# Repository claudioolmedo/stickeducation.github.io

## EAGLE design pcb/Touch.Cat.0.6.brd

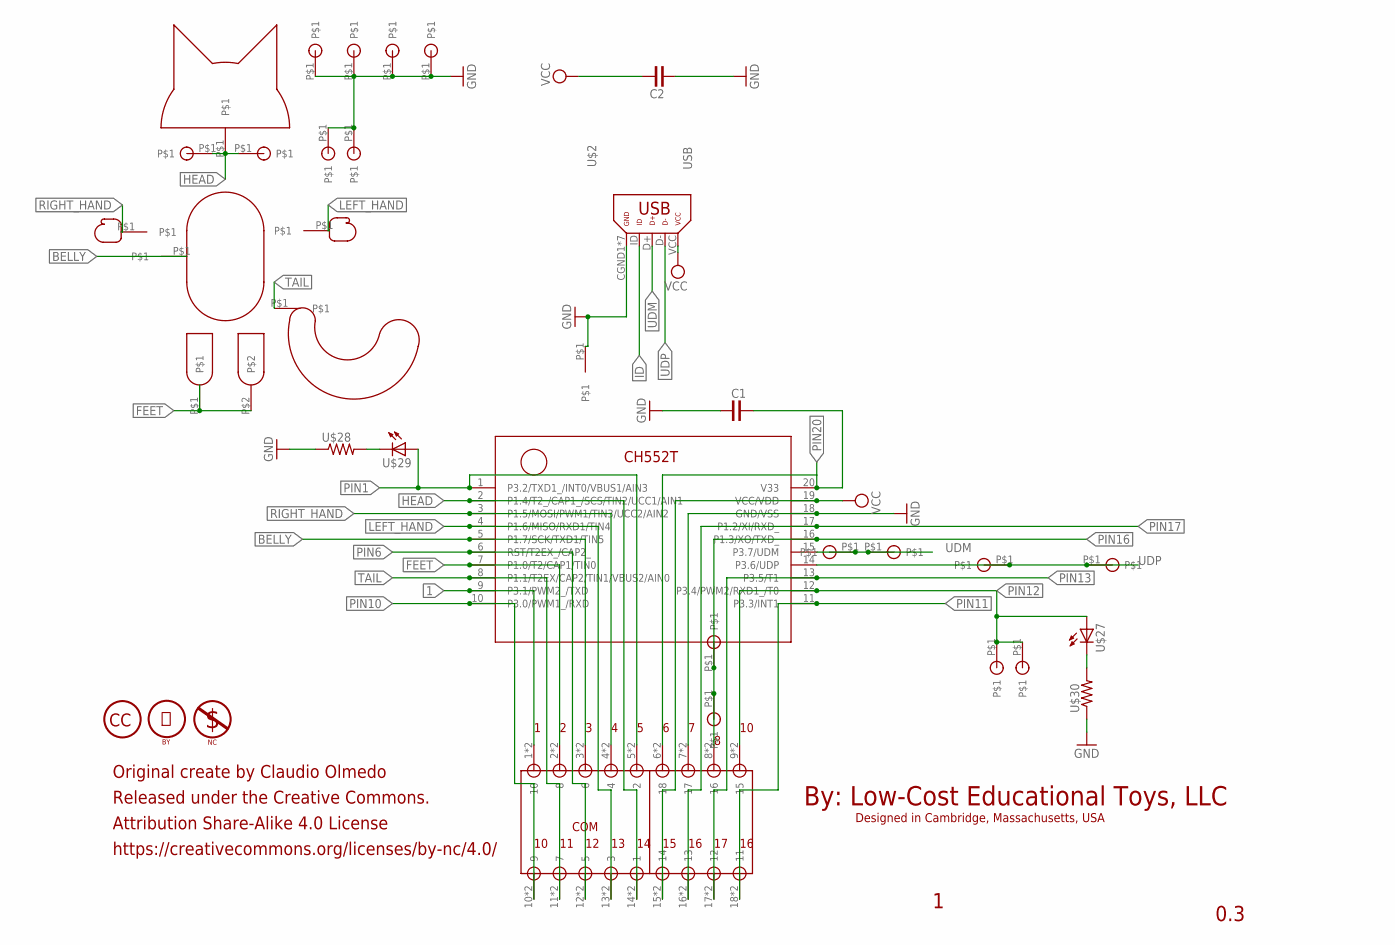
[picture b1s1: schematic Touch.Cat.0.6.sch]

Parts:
C1, C2: CAPACITOR; C0402
U$1: CHIP-TOUCH-CAT; TSSOP20
U$2: USB; GHI-CONNECTORS_10118192-0001LF(MICRO-USB-B-AMPHENOL-FCI)
U$3, U$5, U$6, U$7, U$8, U$9, U$11, U$12, U$13, U$14, U$15, U$16, U$23, U$24, U$25, U$26: PADVIA
U$4: COM-TOUCH-CAT; COM
U$17: HEAD-TOUCH-CAT
U$18: BELLY-TOUCH-CAT
U$19: RIGHT_HAND-TOUCH-CAT
U$20: LEFT_HAND-TOUCH-CAT
U$21: FEET-TOUCH-CAT
U$22: TAIL-TOUCH-CAT
U$27, U$29: LED-TOUCH-CAT; 0603-ORANGE
U$28, U$30: RESISTOR-TOUCH-CAT; R0402
U$31: OSHW-LOGO; OSHW-LOGO-MINI
U$33: ABOUT-TOUCH-CAT

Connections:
1: U$1.9 (P3.1/PWM2_/TXD), U$4.1 (10), U$4.1.1 (10)
BELLY: U$1.5 (P1.7/SCK/TXD1/TIN5), U$4.3 (6), U$4.3.1 (6), U$18.P$1
FEET: U$1.7 (P1.0/T2/CAP1/TIN0), U$4.2 (8), U$4.2.1 (8), U$21.P$1, U$21.P$2
GND: C1.1, C2.1, U$1.18 (GND/VSS), U$2.CGND1 (GND), U$2.CGND2 (GND), U$2.CGND3 (GND), U$2.CGND4 (GND), U$2.CGND5 (GND), U$2.CGND6 (GND), U$2.GND, U$4.7 (17), U$4.7.1 (17), U$6.P$1, U$7.P$1, U$23.P$1, U$24.P$1, U$25.P$1, U$26.P$1, U$28.1, U$30.1, U$31.P$1
HEAD: U$1.2 (P1.4/T2_/CAP1_/SCS/TIN2/UCC1/AIN1), U$4.14 (1), U$4.14.1 (1), U$8.P$1, U$9.P$1, U$17.P$1
ID: U$2.ID
LEFT_HAND: U$1.4 (P1.6/MISO/RXD1/TIN4), U$4.13 (3), U$4.13.1 (3), U$20.P$1
unnamed: U$27.C, U$30.2
unnamed: U$28.2, U$29.C
PIN1: U$1.1 (P3.2/TXD1_/INT0/VBUS1/AIN3), U$4.5 (2), U$4.5.1 (2), U$29.A
PIN6: U$1.6 (RST/T2EX_/CAP2_), U$4.12 (5), U$4.12.1 (5)
PIN10: U$1.10 (P3.0/PWM1_/RXD), U$4.10 (9), U$4.10.1 (9)
PIN11: U$1.11 (P3.3/INT1), U$4.18 (11), U$4.18.1 (11)
PIN12: U$1.12 (P3.4/PWM2/RXD1_/T0), U$3.P$1, U$4.9 (15), U$4.9.1 (15), U$5.P$1, U$27.A
PIN13: U$1.13 (P3.5/T1), U$4.17 (12), U$4.17.1 (12)
PIN16: U$1.16 (P1.3/XO/TXD_), U$4.8 (16), U$4.8.1 (16), U$11.P$1, U$12.P$1
PIN17: U$1.17 (P1.2/XI/RXD_), U$4.16 (13), U$4.16.1 (13)
PIN20: C1.2, U$1.20 (V33), U$4.6 (18), U$4.6.1 (18)
RIGHT_HAND: U$1.3 (P1.5/MOSI/PWM1/TIN3/UCC2/AIN2), U$4.4, U$4.4.1 (4), U$19.P$1
TAIL: U$1.8 (P1.1/T2EX/CAP2/TIN1/VBUS2/AIN0), U$4.11 (7), U$4.11.1 (7), U$22.P$1
UDM: U$1.15 (P3.7/UDM), U$2.D+, U$13.P$1, U$14.P$1
UDP: U$1.14 (P3.6/UDP), U$2.D-, U$15.P$1, U$16.P$1
VCC: C2.2, U$1.19 (VCC/VDD), U$2.VCC, U$4.15 (14), U$4.15.1 (14)

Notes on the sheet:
By: Low-Cost Educational Toys, LLC
0.3
Released under the Creative Commons.
Attribution Share-Alike 4.0 License
https://creativecommons.org/licenses/by-nc/4.0/
Designed in Cambridge, Massachusetts, USA
Original create by Claudio Olmedo

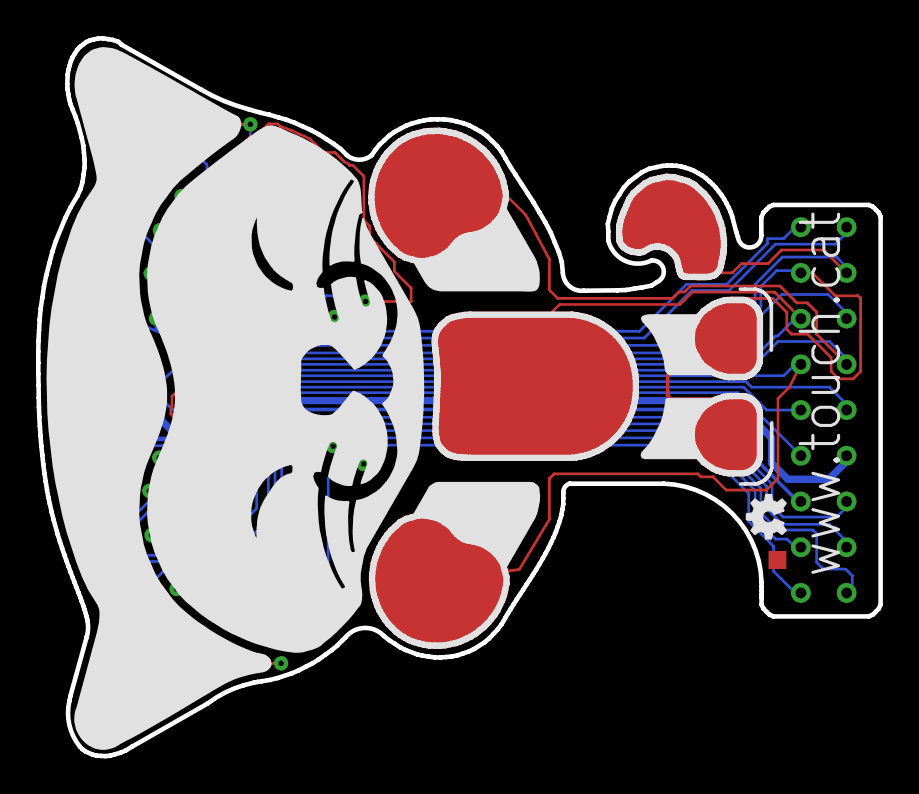
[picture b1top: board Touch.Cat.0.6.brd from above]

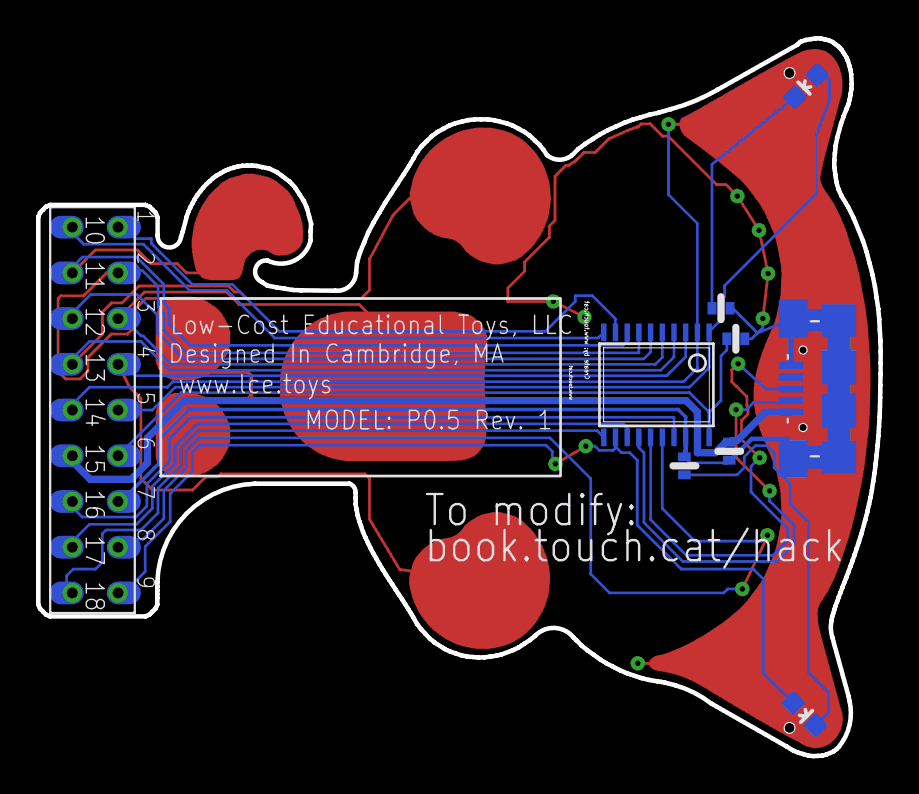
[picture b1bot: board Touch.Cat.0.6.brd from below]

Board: 2 copper layers, 46.8 x 39.9 mm, 33 parts (8 on the bottom side), 22 nets.

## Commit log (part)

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2024-06-09 FORK Button
2024-06-09 Add button
2024-06-09 Revert "Forked project"
    This reverts commit 219d94ef014467ebf30caa72584da5fcda3c1e21.
2024-06-09 add front
2024-06-09 move button
2024-06-09 Revert "add button idFORK"
    This reverts commit b50f3598abbacb2bd795d2f7a53b1b00e5fdfc06.
2024-06-09 Test new rule firebase users
2024-06-09 Update Auth
2024-06-09 Create new link for FORK project
2024-06-10 hide the project button
2024-06-10 add testing Toolbar check
2024-06-10 update the Toolbar component to handle updates:
2024-06-10 Add firebaseDB on the import firebase.js
2024-06-10 Eliminate extra fork-button
2024-06-10 Fixed updateToolbar
2024-06-10 import onAuthStateChanged
2024-06-10 Revert "import onAuthStateChanged"
    This reverts commit 32ab2515ec3ae102df96d2c6f08f525b48d4f2a7.
2024-06-10 Revert "Fixed updateToolbar"
    This reverts commit 9526200dc3caa174453517c8802cb499c4305fc2.
2024-06-10 Revert "Eliminate extra fork-button"
    This reverts commit fc2680cc5e8c61a388a43700ec2df0a8b60bbb7c.
2024-06-10 Revert "Add firebaseDB on the import firebase.js"
    This reverts commit a5adabc3d3b3c61c061e45b345f50feb31baf269.
2024-06-10 Revert "update the Toolbar component to handle updates:"
    This reverts commit 9eae6e9ea8d92e4afd520da7d7ba90d4c10669d5.
2024-06-10 Revert "add testing Toolbar check"
    This reverts commit 8379b6e62155da6a67168fa24b028ce01dee41c7.
2024-06-10 Revert "hide the project button"
    This reverts commit 7fb295577483180540f44946e63964561fc119aa.
2024-06-10 Revert "Create new link for FORK project"
    This reverts commit 3ffa41b829527fd2d067b3f9cf1703cd6e71bc2b.
2024-06-10 Revert "Update Auth"
    This reverts commit 1d60ee014545bdae6d5c83d66f463427ddb29715.
2024-06-10 Revert "Test new rule firebase users"
    This reverts commit ca458df6e727259e23f9f14e1785f46fbf466d3e.
2024-06-10 Reapply "add button idFORK"
    This reverts commit b23b4df315eb198e66cc026fbcea6e85784686de.
2024-06-10 Add ownerId to projects
2024-06-10 "FORK" Button to Toolbar (left side)
2024-06-11 test ownerId
2024-06-11 Revert "Owner or Not"
    This reverts commit b46a69bae10a3ede2311c328d27bbfe17839de37.
2024-06-11 NO OWNER
2024-06-11 is Read Only for no USER
2024-06-11 test no save in firebase if no owner
2024-06-11 Reapply "is Read Only for no USER"
    This reverts commit 5f43690326c5c1d3f3589c3cff659b61ccf89738.
2024-06-11 Revert "fixed bug"
    This reverts commit 88be0c6a9abc40043deaa7fb00c31d44cb79375a.
2024-06-11 forkAction solve bug FORK Button
2024-06-11 Revert "Fixed bug"
    This reverts commit ce5844383ee78a539affbb674f9df05b92d11cbc.
2024-06-11 test owner test
2024-06-11 Revert "fixed bug for have owner"
    This reverts commit 856ea7a18c79d134ad57414714e734facb418c77.
2024-06-11 ownerId login check before save
2024-06-11 Revert "To show the "FORK" button in Toolbar.js when the project has no owner (NO OWNER)"
    This reverts commit 3764ee063a926d523625d13dddecc3904539b9cd.
2024-06-11 Revert "button FORK"
    This reverts commit 9a20c1368773889ab964ce9cc713eddef20e5fea.
2024-06-12 Ad Signalss
2024-06-12 fixed bug name Signal and sinalds
2024-06-12 add mudles
2024-06-12 showForkButton signal received
2024-06-12 Revert "test"
    This reverts commit 2d46c6ed658feefb79dd97a0860aadabfa6c5475.
2024-06-12 Revert "Add Signals to Editor.js"
    This reverts commit f3a9a8320ee96db73ee87e40ddd31e8f62d721c0.
2024-06-12 Revert "Fixed bug for signals"
    This reverts commit 8c18a1c31da307911a5996c2fcf8da3d968a78e8.
2024-06-12 Revert "conditional for show FORK button"
    This reverts commit c93e3b3f1de6a7a8e0a09663963d85edac857455.
2024-06-12 Reapply "To show the "FORK" button in Toolbar.js when the project has no owner (NO OWNER)"
    This reverts commit 60e4a6948c1f83c891e3d61aea801d18de9dd3ae.
2024-06-12 impor signals for push button
2024-06-12 fix bug signals
2024-06-12 Revert "import Signal"
    This reverts commit 34e8fd3ab3764f7ac4281b30bfac9f507a8bb0cc.
2024-06-12 Revert "Hide FORK button if NO OWNER"
    This reverts commit f4e14cf2615bcba6e7f44a2100f3bd452de75b51.
2024-06-12 check console.log('window.isReadOnly:', window.isReadOnly);
2024-06-12 add check in the
2024-06-12 Test for show button
2024-06-12 change for window.isReadOnly
2024-06-12 login button
2024-06-12 change logic for show or not the button
2024-06-12 Add fork button
2024-06-12 change size fork button
2024-06-12 Add generateNewProjectId
2024-06-13 Revert "And login for user or new user acess"
    This reverts commit ac79c0590eebbec829333f3523ff4520e0eaa08b.
2024-06-13 Revert "Login for user"
    This reverts commit 2e30ebc13dad378ce4edb73d0af5c0ddd04735d7.
2024-06-13 Fixed bug for login
2024-06-13 Revert "Add login"
    This reverts commit a43c0f566e523d9806f4d90a1b0ee9f7d8250786.
2024-06-13 Fixed bugo for show code
2024-06-14 Revert "login fro aces everting"
    This reverts commit 9c36936f33d1d427c40665a2d99709b534ddd979.
2024-06-14 Revert "Add Hide button"
    This reverts commit 40cbb97c093ae620b511fd85700a930163ee2447.
2024-06-14 Revert "Login content for user"
    This reverts commit 47bf8b0d009043c1de3db3bb08bdbbc316bf406f.
2024-06-14 add logout button
2024-06-14 Add popsicle stick backgroud
2024-06-14 change to login button image
2024-06-14 Add favicon
2024-06-14 test if work button
2024-06-15 fixed bug login
2024-06-15 Revert "Move fork button to front"
    This reverts commit 168f9d7dc2a5154e8e0e6fb4879fe04bd9104b8c.
2024-06-15 Revert "check fork button"
    This reverts commit f76c2cb2cd524508935a2087b25b09aa6ba973d1.
2024-06-15 move position fork button
2024-06-15 Fixed bug for button FORK show if no have
2024-06-15 test hide the FORK Button
2024-06-15 change name local database for project id
2024-06-16 Fix bug read front firebase
2024-06-16 Revert "receive front database the project"
    This reverts commit 9ee97c6918a008b11cc3042bfc11ebdb886f98af.
2024-06-16 test for read from database
2024-06-16 logic to read an save from database
2024-06-18 Add compare database
2024-06-20 Revert "Save date in project only"
    This reverts commit e03f316d55d2ab57eef2646b6ca91273ed22a707.
2024-06-20 Log Save the project data under the user's
2024-06-20 no save data in user
2024-06-20 Revert "add log"
    This reverts commit 2350ba4acdda4539202713f6529646fc2f1f4b21.
2024-06-20 back
2024-06-20 receive project from firebase only from project
2024-06-20 same data from firebase
2024-06-20 Revert "compare data"
    This reverts commit 74ddd60eb9a0ed663cb012dd766eb02ea512db05.
2024-06-20 Revert "update from firebase realtime"
    This reverts commit c63f98feaa6b6fe06b7118e3e03aa2ce22297403.
2024-06-20 Revert "same data from firebase"
    This reverts commit a8807f9443e67eb6be8cfc00e0762050abdb5cf7.
2024-06-20 fixed bug for firebase
2024-06-20 Revert "broke code"
    This reverts commit d2f531548f36fdefd9b932a524ebceb1f9852ce4.
2024-06-20 Revert "fixed bug for firebase"
    This reverts commit cd59513913789eb3fc96e14a4b3b8b39e79339a2.
2024-06-20 solve
2024-06-20 test firebase
2024-06-20 test for firebase
2024-06-21 Revert "test for firebase"
    This reverts commit f30b2386332f1b12f06e292e2b9ee2e3d948c497.
2024-06-21 clean data for firebase
2024-06-21 Only save in projects w fork button and logics
2024-06-21 creationDate fixed bug
2024-06-22 To restrict users from modifying data in Firebase if they are not the owner,
2024-06-22 Check if the current user is the owner
2024-06-23 Add logic for save forkFrom
2024-06-23 Revert "Fixed bug"
    This reverts commit a487f37612524e18906fbf25a83daa707aebcb77.
2024-06-23 forkeds IDs
2024-06-23 Fixed no delete the forkfrom
2024-06-23 Remove forkFrom field and simplify forking process
    This update removes all references to the 'forkFrom' field, as it's no longer needed. The forking process now relies solely on the 'forkedIDs' array to track project relationships. Key changes includ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
    - Removed 'forkFrom' field from data saving and retrieval processes
    - Updated forkProject() function to only use 'forkedIDs'
    - Simplified data cleaning process by removing 'forkFrom' checks
    - Streamlined Firebase data structure to exclude 'forkFrom'
    These changes improve code clarity and maintain project lineage tracking through the 'forkedIDs' array.
2024-06-23 Add unique ID to project creation
    - Implement generateUniqueId() function
    - Combine timestamp and random string for uniqueness
    - Add uniqueId field to project data in Firebase
    - Apply uniqueId to both new and existing projects
    - Ensure project uniqueness even if created simultaneously
2024-06-24 Fix script handling and unique ID generation
    - Add error handling in Sidebar.Scene.js for undefined scripts
    - Implement generateUniqueId function in Storage.js
    - Update Storage.js to use generateUniqueId when saving data
    - Improve error logging and handling in script-related functions
    - Address issues with IndexedDB and Firebase data synchronization
    - Enhance robustness of data saving and retrieval processes
2024-06-24 Fixed bug for scripts
2024-06-24 Back original code Sidebar.Script
2024-06-24 Revert "back old version"
    This reverts commit 3c5d7519c3313206cb6ebd759088640bf009a2b0.
2024-06-24 Revert "check code"
    This reverts commit 5c173931c64cb408422b190f21248072212af0da.
2024-06-24 Revert "Initialize and handle editor.scripts properly"
    This reverts commit b9bd6c06d464dcde0f2d68d5fb000f35c44c9a43.
2024-06-24 Add logs for check add sticks
2024-06-25 Revert "Fetch data from Firebase"
    This reverts commit 58edd478da36ef687fcc16d4bbbd7dcd8eb23201.
2024-06-26 // Access the IndexedDB API from the window object
2024-06-26 test indexDB loger
2024-06-26 add compare in the html
2024-06-26 add collor for compare
2024-06-27 Add date in IndexDB for make test
2024-06-27 fixed location .js
2024-06-28 fixed location StorageTest
2024-06-28 change location StorageTest.js
2024-06-28 add date
2024-06-28 // Function to save data to IndexedDB
2024-06-28 Revert "Update indexDBCompareToFirebase.html"
    This reverts commit 8d72b7ec9ffb77ee48ffdc135549c63721ee6857.
2024-06-28 Add key for update the database test
2024-06-28 Revert "Ensure keyPath is set"
    This reverts commit 91741dd8d48d4aca822136095262a12b9c681b7d.
2024-06-28 Clone to IndexedDB
2024-06-28 clearIndexedDB eliminate
2024-06-28 add logs
2024-06-30 add name for display the database name
2024-06-30 Add date to firebase
2024-06-30 Add for vizualise the data
2024-06-30 Improve vizualization
2024-06-30 Add logo
2024-06-30 add to list all database
2024-07-01 Add to save data in firebase
2024-07-01 Revert "compareWithIndexedDB"
    This reverts commit 9a34cb10d22a2ce5db406ba338f0aba7518b7b16.
2024-07-01 Fixed bug for set database
2024-07-01 fixed bug save data
2024-07-01 include database name
2024-07-01 Add login and firebase config
2024-07-01 Add to projectId for the database name
2024-07-01 Add StorageOnline
2024-07-02 declare the function as a method of an object.
2024-07-02 console logs at key points in both Storage.js and StorageOnline.js.
2024-07-02 Fixed bug png
2024-07-02 fixed bug in manifest images
2024-07-02 Revert "define or import these functions to resolve the errors."
    This reverts commit 03d7c63bb47308817f57b13f9dfc13b346490223.
2024-07-02 Revert "database instance is properly"
    This reverts commit 6ad14273cc450911db4c1d4c778b3e8ccd14276e.
2024-07-02 Storage
2024-07-02 Save in Firebase using StorageOnline
2024-07-02 Add date from Storage to StorageONline
2024-07-02 Revert "Save in Firebase using StorageOnline"
    This reverts commit cd2d18907d66b9477fa5ff1e98a112fa8142d44c.
2024-07-02 save projeto to firebase using firebase.js
2024-07-02 Revert "Add check for projectId"
    This reverts commit 937318a8f896f067cda734817952a4b522842fd8.
2024-07-02 Import projectId from Storage.js
2024-07-02 projectId receive from StorageOnline
2024-07-02 change format for save in firebase
2024-07-02 export projectId
2024-07-02 Revert "Add StorageOnlineLoad"
    This reverts commit 7c9cee46d30be4d9da2957d4463d2368d9eb5b07.
2024-07-02 back to save project
2024-07-02 Add send projectID to StorageOnlineLoad
2024-07-02 Revert "Save in testX for test"
    This reverts commit ec9be42d759f2f2606c246b37b0dbd8c5f6081d6.
2024-07-03 add database get
2024-07-03 Add other column for select
2024-07-03 Add log for save data in firebase
2024-07-03 Save in firebase if is null
2024-07-03 receive and save data from firebase
